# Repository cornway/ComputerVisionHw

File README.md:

## PCB deisgns with focus on computer vision for embedded devices

I will be publishing here open-source kicad PCB designs, with primary focus on computer vision for embedded (MCU)

Boards available:

1. stm32u5_v1.0 - utilizing stm32u5g9jxx mcu + ov2640 compatible camera and spi display; This board was made using schematics from stm32u5g9j_dk2 and stm32h7 "WeAct" development board
2. stm32u5_v2.0 - simplified version of stm32u5_v1.0, but seems target mcu is out of stock
3. stm32n6_v1.0 - based upon stm32n6xx nucleo development board, no psram yet; Length equalization tables for both xspi can be found in "Resources" directory

Each board is validated, to the best o my knowledge, but may have some issues.
Each board can be manufactured at JLCPCB (each component contains apropriate symbol designator) using Kicad add-on **com.github.bennymeg.JLC-Plugin-for-KiCad**, or in any other preferred way. Key point was to produce easy to understand design, that can be manufactured at low cost and used for further prototyping

Example (and not only) software for these boards can be found here :

https://github.com/cornway/ComputerVisionEmbedded

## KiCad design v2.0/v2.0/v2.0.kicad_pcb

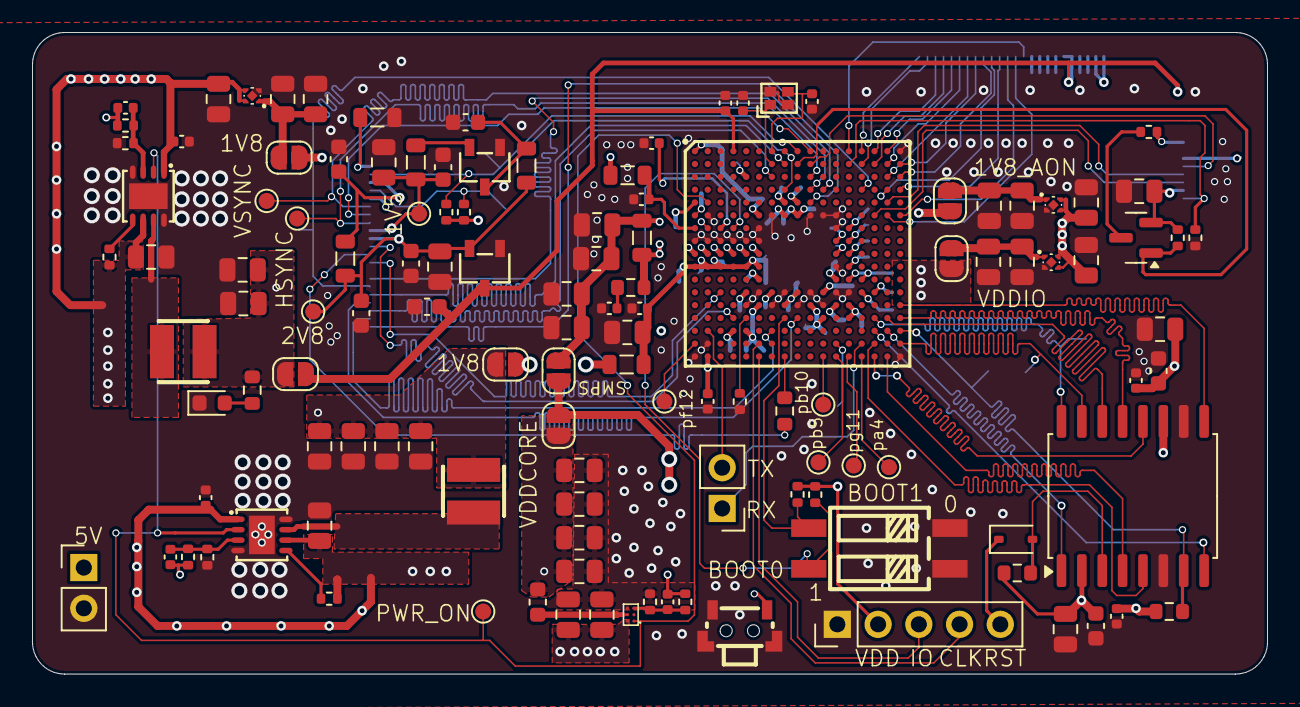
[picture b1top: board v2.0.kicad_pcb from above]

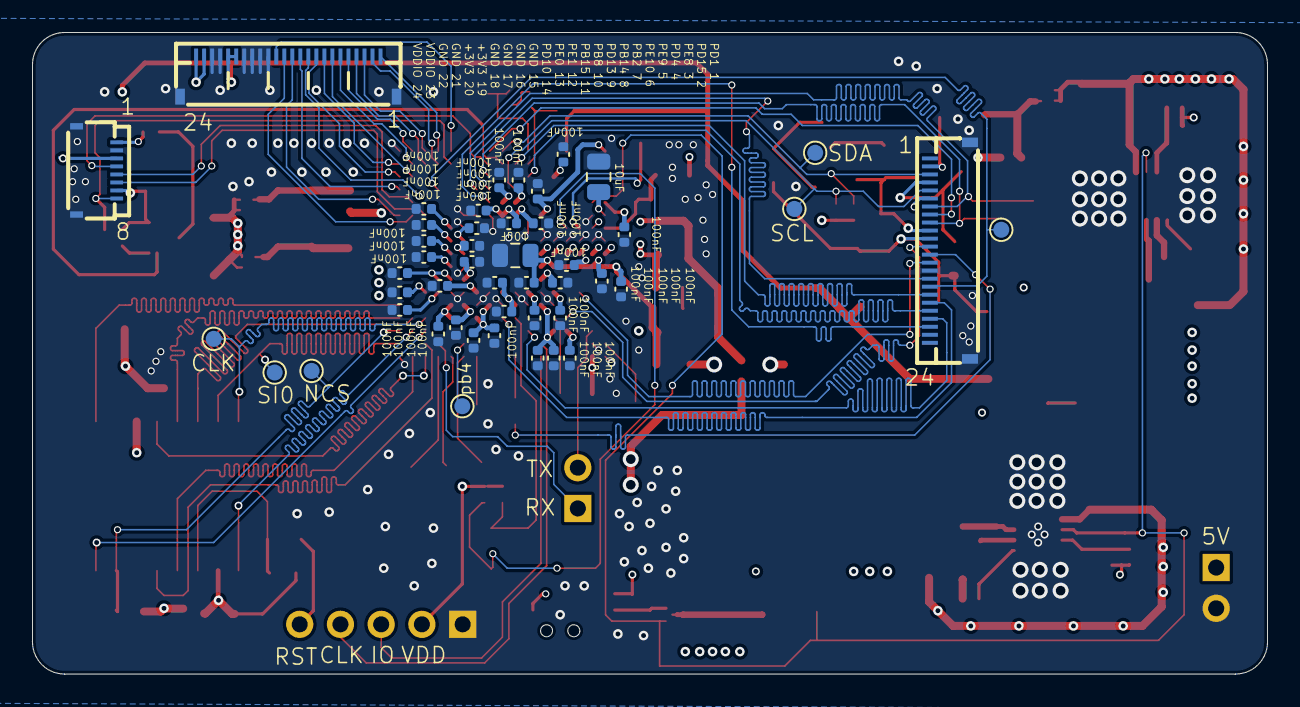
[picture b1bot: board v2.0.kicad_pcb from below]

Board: 4 copper layers, 77.0 x 40.0 mm, 170 parts (47 on the bottom side), 101 nets.

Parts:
C1, C6, C12, C15, C17, C18, C19, C20, C21, C22, C23, C25, C26, C27, C28, C29, C30, C31, C32, C33, C34, C35, C36, C37, C38, C39, C40, C41, C42, C43, C44, C45, C46, C47, C80, C81: 100nF; C_0402_1005Metric
C2, C4, C13, C14, C16, C51, C52: 1uF; C_0402_1005Metric
C3, C7, C9, C10, C54, C55, C56, C57, C58, C59, C60, C61, C63, C64: 22uF; C_0805_2012Metric
C5: 2.2nF; C_0402_1005Metric
C8, C11, C24, C48, C49, C50, C53, C90: 10uF; C_0805_2012Metric
C62, C65: 22p; C_0402_1005Metric
C66: 100pF; C_0402_1005Metric
C67, C68, C69, C70, C71, C72, C73, C74, C75: 1uF; C_0805_2012Metric
C76, C77: 4.7uf; C_0603_1608Metric
C78, C79, C84, C87: 10uf; C_0805_2012Metric
C82, C83, C86, C89: 1uf; C_0603_1608Metric
C85, C88: 100nf; C_0603_1608Metric
C91, C93: 8.2pF; C_0402_1005Metric
C92: 10nF; C_0402_1005Metric
D1: LED; LED_0603_1608Metric
D2: BAT60A; D_SOD-323
IC1: STM32N657X0H3Q; BGA264C80P17X17_1400X1400X100
J1: Conn_01x05_Pin; PinHeader_1x05_P2.54mm_Vertical
J2, J3: Conn_01x02_Pin; PinHeader_1x02_P2.54mm_Vertical
JP1, JP2, JP3, JP4, JP5, JP6, JP7: SolderJumper_2_Open; SolderJumper-2_P1.3mm_Open_RoundedPad1.0x1.5mm
L1: 1.0uH; L_0805_2012Metric
L2: 18@100Mhz; L_0805_2012Metric
L3: 2.2nH; L_0805_2012Metric
L4: 240nH; L_0603_1608Metric
L5, L6: 2.2uH; IND-SMD_L3.0-W3.0
L7, L8, L9, L10: 1.5uH; L_0805_2012Metric
Q1: SOT-23
R1, R2: 1k5; R_0402_1005Metric
R3, R4, R7, R8, R21: 10k; R_0402_1005Metric
R5: 2R; R_0603_1608Metric
R6: 200R; R_0402_1005Metric
R9: 75k; R_0402_1005Metric
R10, R15: 24k; R_0402_1005Metric
R11: 56k2; R_0402_1005Metric
R12: 160k; R_0402_1005Metric
R13: 5.1k; R_0603_1608Metric
R14: 30k; R_0402_1005Metric
R16: 10K; R_0603_1608Metric
R17: 100K; R_0603_1608Metric
R18: 33R; R_0603_1608Metric
R19: 100k; R_0402_1005Metric
R20: 22R; R_0402_1005Metric
SCL1: TestPoint; TestPoint_Pad_D1.0mm
SDA1: TestPoint; TestPoint_Pad_D1.0mm
SW1: SW-SMD_YZA-021
TP1, TP2, TP3, TP4, TP5, TP6, TP7, TP8, TP9, TP10, TP11, TP12, TP13, TP14, TP15: TestPoint; TestPoint_Pad_D1.0mm
U1: SW-SMD_SMXS-02K-TP
U2, U3: TDFN-8_L3.0-W3.0-P0.65-BL-EP
U4: TPS62088YFP; DSBGA-6_L0.8-W1.2-P0.40-R3-C2-TL
U5, U6, U7: UDFN-4_L1.0-W1.0-P0.65-TL
U8: MX66LM1G45G; SOIC-16W_7.5x10.3mm_P1.27mm
U9, U13: FFC-SMD_24P-P0.50_FH34SRJ-24S-0.5SH
U10: XC6206P282MR; SOT-23-3_L2.9-W1.6-P1.90-LS2.8-BR
U11: XC6206P152MR; SOT-23-3_L2.9-W1.6-P1.90-LS2.8-BR
U12: FPC-SMD_8P-P0.50_FH34D-8S-0.5SH-50
X1: -; CRYSTAL-SMD_4P-L1.6-W1.2-BL

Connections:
+3V3: C4.2, C82.1, C90.1, IC1.A4 (VDD33US_B), JP3.2 (B), Q1.2 (S), R21.1, U10.3 (VIN), U12.7, U13.19, U13.20
+5V: C48.1, C49.1, C50.1, C51.1, C52.1, C53.1, C67.1, C68.1, C69.1, J3.1, R7.1, R8.1, U2.1 (VINA), U2.6 (VINSW), U3.1 (VINA), U3.6 (VINSW), U4.A2 (VIN), U5.3 (EN), U5.4 (VIN), U6.3 (EN), U6.4 (VIN), U7.3 (EN), U7.4 (VIN)
/Flash/SI0: IC1.T17 (PN2), TP3.1, U8.15 (SI/SIO0)
/Flash/SI1: IC1.R15 (PN3), U8.8 (SO/SIO1)
/Flash/SI2: IC1.N17 (PN4), U8.9 (SIO2)
/Flash/SI3: IC1.R16 (PN5), U8.1 (SIO3)
/Flash/SI4: IC1.P16 (PN8), U8.14 (SIO4)
/Flash/SI5: IC1.T15 (PN9), U8.5 (SIO5)
/Flash/SI6: IC1.U15 (PN10), U8.12 (SIO6)
/Flash/SI7: IC1.U16 (PN11), U8.4 (SIO7)
/I2C1_SCL: IC1.D8 (PH9), R2.1, SCL1.1, U9.5
/I2C1_SDA: IC1.A9 (PC1), R1.1, SDA1.1, U9.3
/LCD/LCD_CS: IC1.B13 (PE7), R19.1, U12.8
/LCD/LCD_LEDA: R20.2, U12.1
/LCD/LCD_SCL: IC1.F15 (PE2), U12.6
/LCD/LCD_SDA: IC1.E16 (PB7), U12.5
/LCD/LCD_WR_RS: IC1.B10 (PC5), U12.4
/LCD/lcd_led: IC1.B9 (PC6), Q1.1 (G), R21.2
/MCU/BOOT0: IC1.G4 (BOOT0), R4.2, U1.4
/MCU/BOOT1: IC1.P8 (PA6), R3.2, U1.3
/MCU/DCMI_D0: IC1.P9 (PA1), U9.19
/MCU/DCMI_D1: IC1.R7 (PA10), U9.21
/MCU/DCMI_D2: IC1.E10 (PC3), U9.22
/MCU/DCMI_D3: IC1.C7 (PC9), U9.20
/MCU/DCMI_D4: IC1.B8 (PC11), U9.18
/MCU/DCMI_D5: IC1.D10 (PE4), U9.16
/MCU/DCMI_D6: IC1.M3 (PF5), U9.14
/MCU/DCMI_D7: IC1.P4 (PF1), U9.12
/MCU/DCMI_HSYNC: IC1.C10 (PC0), TP5.1, U9.9
/MCU/DCMI_PIXCLK: IC1.D14 (PD5), TP6.1, U9.17
/MCU/DCMI_VSYNC: IC1.D11 (PE6), TP4.1, U9.7
/MCU/MCO: IC1.U8 (PA8), R18.2
/MCU/OSC_IN: C93.2, IC1.A7 (PH0-_OSC_IN), X1.3 (OSC2)
/MCU/OSC_OUT: C91.1, IC1.B7 (PH1-_OSC_OUT), X1.1 (OSC1)
/MCU/OSPI_CLK: IC1.P15 (PN6), TP2.1, U8.16 (SCLK)
/MCU/OSPI_DQS: IC1.P17 (PN0), U8.13 (DQS)
/MCU/OSPI_NCS: IC1.R17 (PN1), R16.2, TP1.1, U8.7 (CS)
/MCU/PB2: IC1.C16 (PB2), U13.7
/MCU/PB8: IC1.D16 (PB8), U13.10
/MCU/PB14: IC1.B17 (PB14), U13.8
/MCU/PB15: IC1.D17 (PB15), U13.11
/MCU/PD1: IC1.A14 (PD1), U13.1
/MCU/PD4: IC1.B15 (PD4), U13.4
/MCU/PD10: IC1.A13 (PD10), U13.14
/MCU/PD13: IC1.C17 (PD13), U13.9
/MCU/PD15: IC1.B14 (PD15), U13.2
/MCU/PE0: IC1.F16 (PE0), U13.13
/MCU/PE1: IC1.F17 (PE1), U13.12
/MCU/PE8: IC1.A15 (PE8), U13.3
/MCU/PE9: IC1.A16 (PE9), U13.5
/MCU/PE10: IC1.B16 (PE10), U13.6
/MCU/PORTC_4: IC1.A10 (PC4), U9.8
/MCU/SWCLK: IC1.T6 (PA14), J1.4
/MCU/SWDIO: IC1.U6 (PA13), J1.3
/MCU/USART1_RX: IC1.T14 (PG8), J2.1
/MCU/USART1_TX: IC1.R2 (PF13), J2.2
/MCU/VDDA1V8PMU: C2.2, IC1.G1 (VDDA18P_MU), L2.2
/MCU/VDDSMPS: C11.1, C13.1, C14.1, C16.1, C19.1, C22.1, C24.1, IC1.K1 (VDDSMPS_1), IC1.K2 (VDDSMPS_2), IC1.K3 (VDDSMPS_3), IC1.K4 (VDDSMPS_4), IC1.K5 (VDDSMPS_5), IC1.K6 (VDDSMPS_6), L3.1
/MCU/VFBSMPS: C3.1, C7.1, C9.1, C10.1, IC1.G2 (VFBSMPS), JP7.1 (A), L1.2
/MCU/VLXSMPS: IC1.J1 (VLXSMPS_1), IC1.J2 (VLXSMPS_2), IC1.J3 (VLXSMPS_3), IC1.J4 (VLXSMPS_4), IC1.J5 (VLXSMPS_5), IC1.J6 (VLXSMPS_6), L1.1, R5.1
/RESET: C92.1, D2.1 (K), IC1.G3 (NRST), J1.5, SW1.1, U9.6, U12.3
/VDDA_1V8: C15.1, C21.1, C26.1, C29.1, C31.1, C34.1, IC1.C5 (VDDA18U_SB), IC1.M5 (VDDA18P_LL), IC1.N6 (VDDA18A_DC), IC1.N13 (VDDIO3_1), IC1.P13 (VDDIO3_2), IC1.R5 (VDDA18C_SI), IC1.U2 (VREF+), JP5.2 (B), L2.1
/VDDA_1V8_AON: C6.2, IC1.A1 (PDR_ON), IC1.F6 (VDDA18A_ON), JP1.2 (B)
/VDDCORE: C18.1, C23.1, C27.1, C30.1, C33.1, C36.1, C38.1, C40.1, C42.1, C43.1, IC1.L6 (VDDCORE_1), IC1.L12 (VDDCORE_2), IC1.M7 (VDDCORE_3), IC1.M9 (VDDCORE_4), IC1.M11 (VDDCORE_5), IC1.N8 (VDDCORE_6), IC1.N10 (VDDCORE_7), IC1.N12 (VDDCORE_8), IC1.P11 (VDDCORE_9), IC1.R4 (VDDCSI), JP6.2 (B), JP7.2 (B)
/VDDIO: C1.2, C12.1, C17.1, C20.1, C25.1, C28.1, C32.1, C35.1, C37.1, C39.1, C41.1, C44.1, C45.1, C46.1, C47.1, IC1.E1 (VBAT), IC1.E8 (VDDIO4_1), IC1.E9 (VDDIO5_1), IC1.F8 (VDDIO4_2), IC1.F9 (VDDIO5_2), IC1.G13 (VDD_1), IC1.H12 (VDD_2), IC1.H13 (VDD_3), IC1.J12 (VDD_4), IC1.J13 (VDD_5), IC1.K13 (VDD_6), IC1.L13 (VDDIO2_1), IC1.L14 (VDDIO2_2), IC1.M14 (VDDIO2_3), IC1.M15 (VDDIO2_4), J1.2, JP2.2 (B), R1.2, R2.2, R3.1, R4.1, U13.23, U13.24
/VDD_1V8: C76.1, C77.1, C78.1, C79.1, C80.1, C81.1, JP4.2 (B), L3.2, R16.1, R17.1, U8.2 (VCC), U8.11 (VCC)
/camera/AGND: L8.1, U9.2
/camera/AVDD-2V8: C89.1, L10.2, U9.4
/camera/DVDD-1V5: C87.1, C88.1, L9.2, TP8.1, U9.10
/camera_power/VDD_2V8: C84.1, C85.1, C86.1, L7.1, L10.1, TP7.1, U9.11, U10.2 (VOUT)
/power/FB: C66.2, R11.2, R12.1, U4.C1 (FB)
/power/FB2: C65.2, R14.2, R15.1, U2.3 (FB)
/power/FB3: C62.2, R9.2, R10.1, U3.3 (FB)
/power/PWR_ON: IC1.E2 (PWR_ON), TP9.1, U2.2 (EN), U3.2 (EN), U4.A1 (EN)
/power/VDDA_1V8: C72.1, C75.1, JP5.1 (A), U7.1 (VOUT)
/power/VDDA_1V8_AON: C71.1, C74.1, JP1.1 (A), U6.1 (VOUT)
/power/VDDCORE: C54.1, C57.1, C60.1, C63.1, C66.1, JP6.1 (A), L4.2, R11.1
/power/VDDIO: C70.1, C73.1, JP2.1 (A), U5.1 (VOUT)
/power/VDD_1V8: C55.1, C58.1, C61.1, C64.1, C65.1, JP4.1 (A), L5.2, R14.1
/power/VDD_3V3: C56.1, C59.1, C62.1, JP3.1 (A), L6.2, R9.1, R13.1
GND: C1.1, C2.1, C3.2, C4.1, C5.2, C6.1, C7.2, C8.1, C9.2, C10.2, C11.2, C12.2, C13.2, C14.2, C15.2, C16.2, C17.2, C18.2, C19.2, C20.2, C21.2, C22.2, C23.2, C24.2, C25.2, C26.2, C27.2, C28.2, C29.2, C30.2, C31.2, C32.2, C33.2, C34.2, C35.2, C36.2, C37.2, C38.2, C39.2, C40.2, C41.2, C42.2, C43.2, C44.2, C45.2, C46.2, C47.2, C48.2, C49.2, C50.2, C51.2, C52.2, C53.2, C54.2, C55.2, C56.2, C57.2, C58.2, C59.2, C60.2, C61.2, C63.2, C64.2, C67.2, C68.2, C69.2, C70.2, C71.2, C72.2, C73.2, C74.2, C75.2, C76.2, C77.2, C78.2, C79.2, C80.2, C81.2, C82.2, C83.2, C84.2, C85.2, C86.2, C87.2, C88.2, C89.2, C90.2, C91.2, C92.2, C93.1, D1.1 (K), IC1.A17 (VSS_1), IC1.F2 (VSSAPMU), IC1.F7 (VSS_2), IC1.F10 (VSS_3), IC1.F11 (VSS_4), IC1.F12 (VSS_5), IC1.G6 (VSSAON), IC1.G12 (VSS_6), IC1.H1 (VSSSMPS_1), IC1.H2 (VSSSMPS_2), IC1.H3 (VSSSMPS_3), IC1.H4 (VSSSMPS_4), IC1.H5 (VSSSMPS_5), IC1.H6 (VSSSMPS_6), IC1.K12 (VSS_7), IC1.M6 (VSSA), IC1.M8 (VSS_8), IC1.M10 (VSS_9), IC1.M12 (VSS_10), IC1.M13 (VSS_11), IC1.N5 (VSS_12), IC1.N7 (VSS_13), IC1.N9 (VSS_14), IC1.N11 (VSS_15), IC1.T2 (VREF-), IC1.U1 (VSS_16), IC1.U17 (VSS_17), J1.1, J3.2, L8.2, R6.2, R10.2, R12.2, R15.2, R19.2, SW1.2, SW1.3, SW1.4, U1.1, U1.2, U2.4 (AGND), U2.8 (PGND), U2.9 (EP), U3.4 (AGND), U3.8 (PGND), U3.9 (EP), U4.C2 (GND), U5.2 (GND), U5.5 (EP), U6.2 (GND), U6.5 (EP), U7.2 (GND), U7.5 (EP), U8.6 (GND), U8.10 (GND), U9.15, U9.25, U9.26, U10.1 (VSS), U11.1 (GND), U12.2, U12.9, U12.10, U13.15, U13.16, U13.17, U13.18, U13.21, U13.22, U13.25, U13.26, X1.2, X1.4
unnamed: C5.1, R5.2
unnamed: D1.2 (A), R13.2
unnamed: D2.2 (A), R17.2, U8.3 (RESET)
unnamed: IC1.P5 (CSI_REXT), R6.1
unnamed: IC1.U14 (PA4), TP10.1
unnamed: IC1.T12 (PB4), TP14.1
unnamed: IC1.U12 (PB5), TP12.1
unnamed: IC1.U11 (PB10), TP13.1
unnamed: IC1.T1 (PF12), TP15.1
unnamed: IC1.U13 (PG11), TP11.1
unnamed: C8.2, IC1.F1 (V08CAP)
unnamed: Q1.3 (D), R20.1
unnamed: R18.1, U9.13
unnamed: R7.2, U2.5 (PG)
unnamed: L5.1, U2.7 (SW)
unnamed: R8.2, U3.5 (PG)
unnamed: L6.1, U3.7 (SW)
unnamed: L4.1, U4.B2 (SW)
unnamed: C83.1, L7.2, U11.3 (Vin)
unnamed: L9.1, U11.2 (Vout)

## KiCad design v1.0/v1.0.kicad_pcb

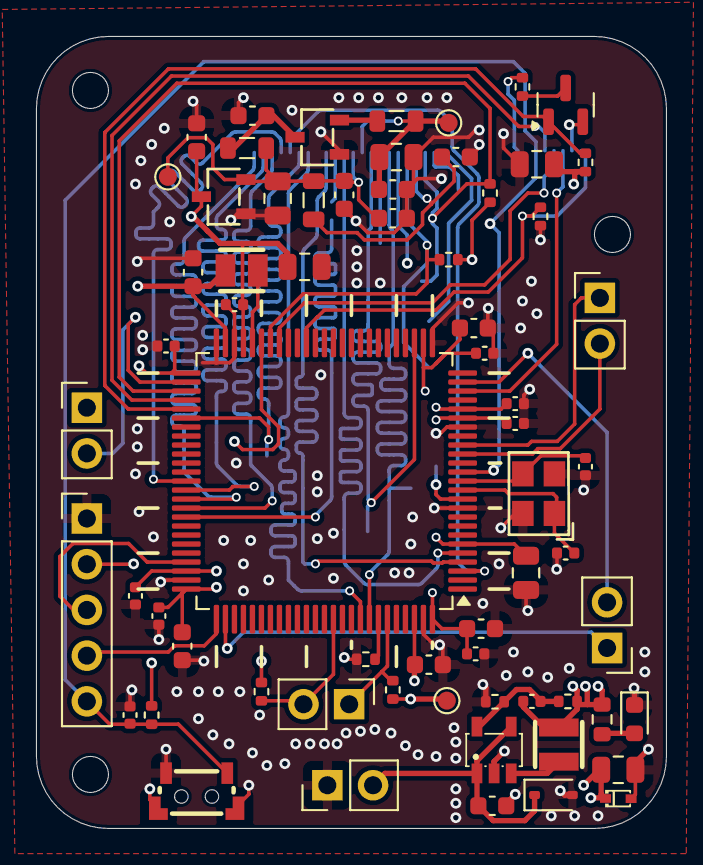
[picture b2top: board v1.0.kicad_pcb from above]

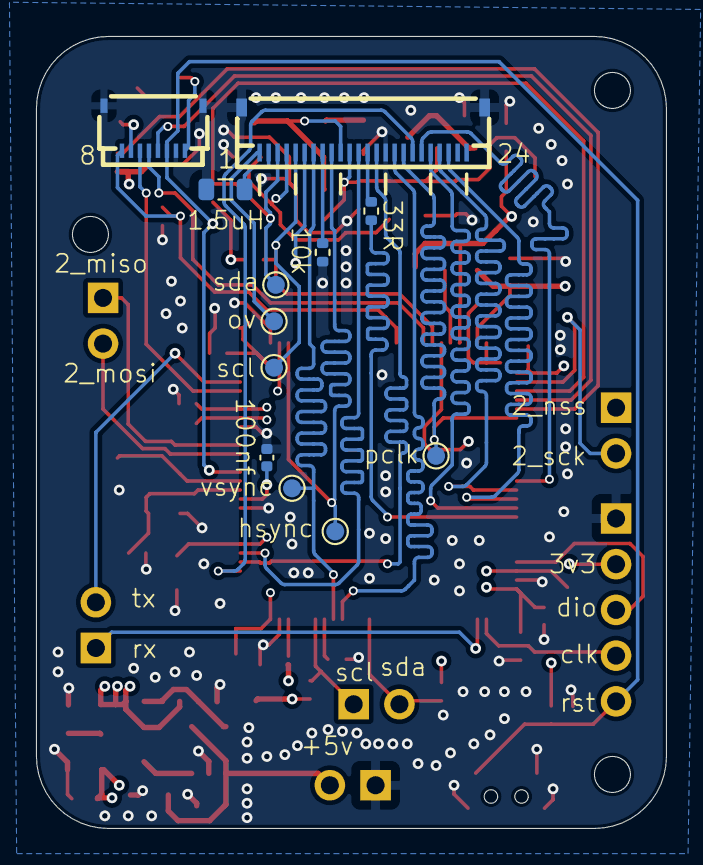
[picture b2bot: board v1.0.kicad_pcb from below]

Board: 4 copper layers, 35.0 x 44.0 mm, 78 parts (12 on the bottom side), 52 nets.

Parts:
C7, C26, C37: 10uF; C_0805_2012Metric
C8: 4.7uf; C_0603_1608Metric
C9, C10, C14, C17: 1uf; C_0603_1608Metric
C11, C13, C18: 10uf; C_0805_2012Metric
C12, C15: 100nf; C_0603_1608Metric
C16: 22pf; C_0402_1005Metric
C19, C22: 8.2pF; C_0402_1005Metric
C24, C29, C30, C32, C33, C34, C38, C39, C40, C41: 100nF; C_0402_1005Metric
C27: 4.7uF; C_0603_1608Metric
C28: 1uF; C_0603_1608Metric
C31: 100nF; C_0603_1608Metric
C35, C36: 2.2uF; C_0603_1608Metric
D3: LESD3Z5.0T1G; D_SOD-323
D4: LED; LED_0603_1608Metric
D5: LESD5Z3.3T1G; SOD-523F_L1.2-W0.8-LS1.7-RD
IC1: STM32U5G7VJT6Q; LQFP-100_14x14mm_P0.5mm
J1: Conn_01x05_Pin; PinHeader_1x05_P2.54mm_Vertical
J3, J4, J5, J6, J7: Conn_01x02_Pin; PinHeader_1x02_P2.54mm_Vertical
L1: 2.2uH; IND-SMD_L2.4-W1.7_NL201614
L2, L3, L5, L6: 1.5uH; L_0805_2012Metric
L4: 2.2uH; IND-SMD_L2.5-W2.0_SWPA252012S
Q2: SOT-23
R11, R12, R24, R25: 4K7; R_0402_1005Metric
R13, R23: 100k; R_0402_1005Metric
R14: 22R; R_0402_1005Metric
R15: 10k; R_0402_1005Metric
R16: 680k; R_0402_1005Metric
R17: 150k; R_0402_1005Metric
R18: 5.1k; R_0603_1608Metric
R19, R21: 10K; R_0402_1005Metric
R20: 33R; R_0402_1005Metric
SCL1: TestPoint; TestPoint_Pad_D1.0mm
SDA1: TestPoint; TestPoint_Pad_D1.0mm
SW1: SW-SMD_YZA-021
TP2, TP3, TP4, TP5, TP6, TP7, TP8: TestPoint; TestPoint_Pad_D1.0mm
U5: FPC-SMD_8P-P0.50_FH34D-8S-0.5SH-50
U6: XC6206P152MR; SOT-23-3_L2.9-W1.6-P1.90-LS2.8-BR
U7: XC6206P282MR; SOT-23-3_L2.9-W1.6-P1.90-LS2.8-BR
U8: SY8088AAC; SOT-23-5_L3.0-W1.7-P0.95-LS2.8-BR
U9: FFC-SMD_24P-P0.50_FH34SRJ-24S-0.5SH
X2: 16MHz; CRYSTAL-SMD_4P-L3.2-W2.5-BL-1

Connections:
+1V5: C13.1, C15.1, L3.2, TP3.1, U9.10
+2V8: C11.1, C12.1, C14.1, L2.1, L5.1, TP2.1, U7.2 (VOUT), U9.11
+3V3: C7.1, C9.1, C16.1, C18.1, C26.2, C27.2, C28.2, C29.2, C30.2, C31.2, C32.2, C33.2, C34.2, C37.2, C38.2, C39.2, C40.2, C41.2, D5.1 (C), IC1.6 (VBAT), IC1.11 (VDD_1), IC1.20 (VREF+), IC1.21 (VDDA), IC1.27 (VDD_2), IC1.47 (VDDSMPS), IC1.51 (VDD_3), IC1.73 (VDDUSB), IC1.75 (VDD_4), IC1.100 (VDD_5), J1.2, L4.2, Q2.2 (S), R11.1, R12.1, R15.1, R16.1, R18.1, R23.1, R24.1, R25.1, TP4.1, U5.7, U7.3 (VIN)
+5V: C8.1, D3.1, J7.2, U8.1 (EN), U8.4 (IN)
/DVP_HSYNC: IC1.28 (PA4), TP6.1, U9.9
/DVP_PCLK: IC1.56 (PD9), TP7.1, U9.17
/DVP_VSYNC: IC1.93 (PB7), TP5.1, U9.7
/DVP_XCLK: IC1.67 (PA8), R20.2
/LCD/LCD_CS: IC1.40 (PE12), R13.1, U5.8
/LCD/LCD_LEDA: R14.2, U5.1
/LCD/LCD_SCL: IC1.23 (PA1), U5.6
/LCD/LCD_SDA: IC1.43 (PE15), U5.5
/LCD/LCD_WR_RS: IC1.54 (PB15), U5.4
/LCD/lcd_led: IC1.55 (PD8), Q2.1 (G), R15.2
/MCU/DCMI_D0: IC1.63 (PC6), U9.19
/MCU/DCMI_D1: IC1.64 (PC7), U9.21
/MCU/DCMI_D2: IC1.65 (PC8), U9.22
/MCU/DCMI_D3: IC1.66 (PC9), U9.20
/MCU/DCMI_D4: IC1.3 (PE4), U9.18
/MCU/DCMI_D5: IC1.92 (PB6), U9.16
/MCU/DCMI_D6: IC1.4 (PE5), U9.14
/MCU/DCMI_D7: IC1.5 (PE6), U9.12
/MCU/I2C1_SCL: IC1.95 (PB8), J6.1, R25.2
/MCU/I2C1_SDA: IC1.89 (PB3), J6.2, R24.2
/MCU/I2C2_SCL: IC1.44 (PB10), R12.2, SCL1.1, U9.5
/MCU/I2C2_SDA: IC1.53 (PB14), R11.2, SDA1.1, U9.3
/MCU/RCC_OSC_IN: C19.1, IC1.12 (PH0-OSC_IN), X2.1 (OSC1)
/MCU/RCC_OSC_OUT: C22.2, IC1.13 (PH1-OSC_OUT), X2.3 (OSC2)
/MCU/SPI2_MISO: IC1.17 (PC2), J5.1
/MCU/SPI2_MOSI: IC1.16 (PC1), J5.2
/MCU/SPI2_NSS: IC1.45 (PB11), J4.1
/MCU/SPI2_SCK: IC1.52 (PB13), J4.2
/MCU/SWCLK: IC1.76 (PA14), J1.4
/MCU/SWDIO: IC1.72 (PA13), J1.3
/MCU/USART2_RX: IC1.77 (PA15), J3.1
/MCU/USART2_TX: IC1.24 (PA2), J3.2
/MCU/VDD11: C35.2, C36.2, IC1.49 (VDD11_1), IC1.98 (VDD11_2), L1.1
/RESET: C24.1, IC1.14 (NRST), J1.5, R23.2, SW1.1, U5.3, U9.6
/camera/AVDD-2V8: C17.1, L5.2, U9.4
/camera/OV_STROBE: TP8.1, U9.1
GND: C7.2, C8.2, C9.2, C10.2, C11.2, C12.2, C13.2, C14.2, C15.2, C17.2, C18.2, C19.2, C22.1, C24.2, C26.1, C27.1, C28.1, C29.1, C30.1, C31.1, C32.1, C33.1, C34.1, C35.1, C36.1, C37.1, C38.1, C39.1, C40.1, C41.1, D3.2, D4.1 (K), D5.2 (A), IC1.10 (VSS_1), IC1.19 (VSSA), IC1.26 (VSS_2), IC1.48 (VSSSMPS), IC1.50 (VSS_3), IC1.74 (VSS_4), IC1.99 (VSS_5), J1.1, J7.1, L6.2, R13.2, R17.2, R19.2, R21.2, SW1.2, SW1.3, SW1.4, U5.2, U5.9, U5.10, U6.1 (GND), U7.1 (VSS), U8.2 (GND), U9.15, U9.25, U9.26, X2.2 (GND), X2.4 (GND)
GNDA: L6.1, U9.2
unnamed: D4.2 (A), R18.2
unnamed: IC1.94 (PH3-BOOT0), R21.1
unnamed: IC1.46 (VLXSMPS), L1.2
unnamed: Q2.3 (D), R14.1
unnamed: R19.1, U9.8
unnamed: R20.1, U9.13
unnamed: C10.1, L2.2, U6.3 (Vin)
unnamed: L3.1, U6.2 (Vout)
unnamed: C16.2, R16.2, R17.1, U8.5 (FB)
unnamed: L4.1, U8.3 (LX)

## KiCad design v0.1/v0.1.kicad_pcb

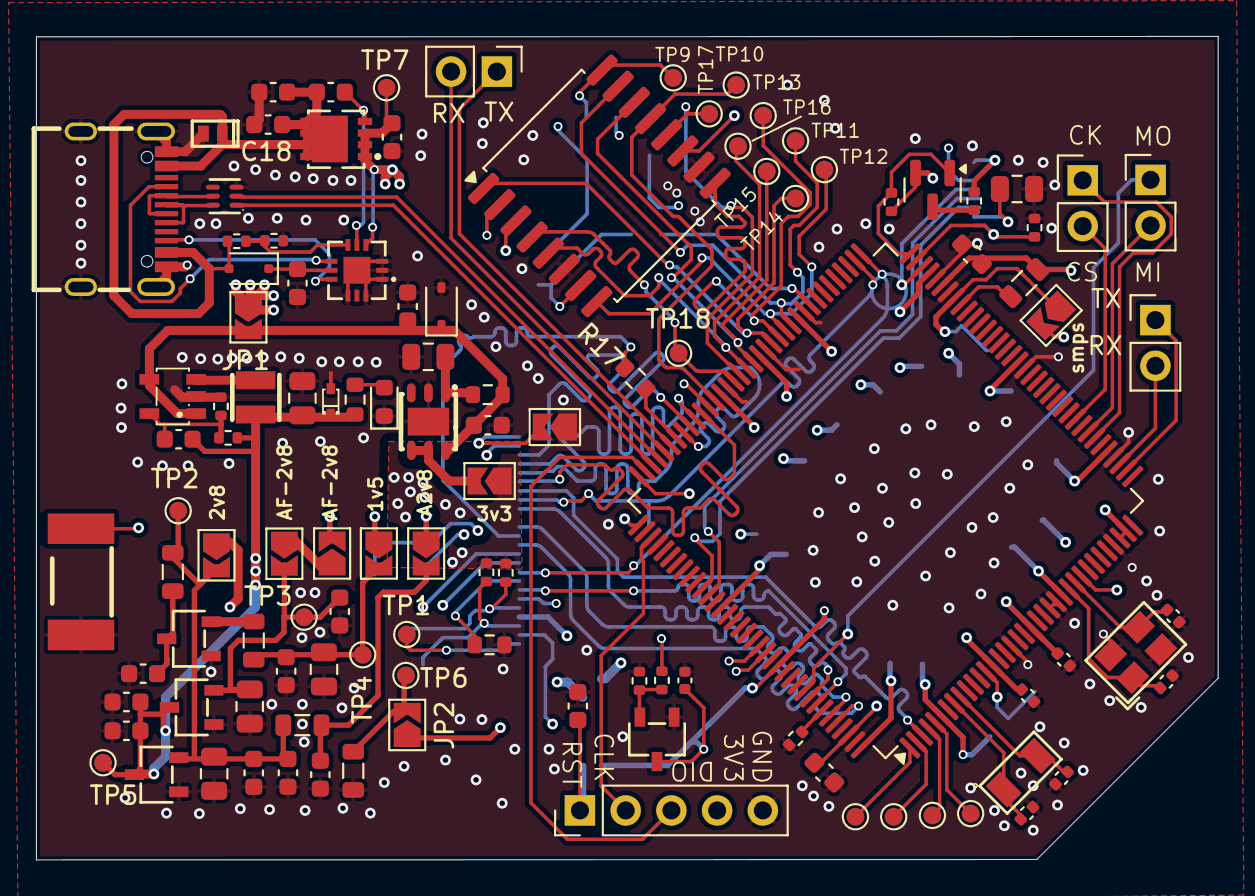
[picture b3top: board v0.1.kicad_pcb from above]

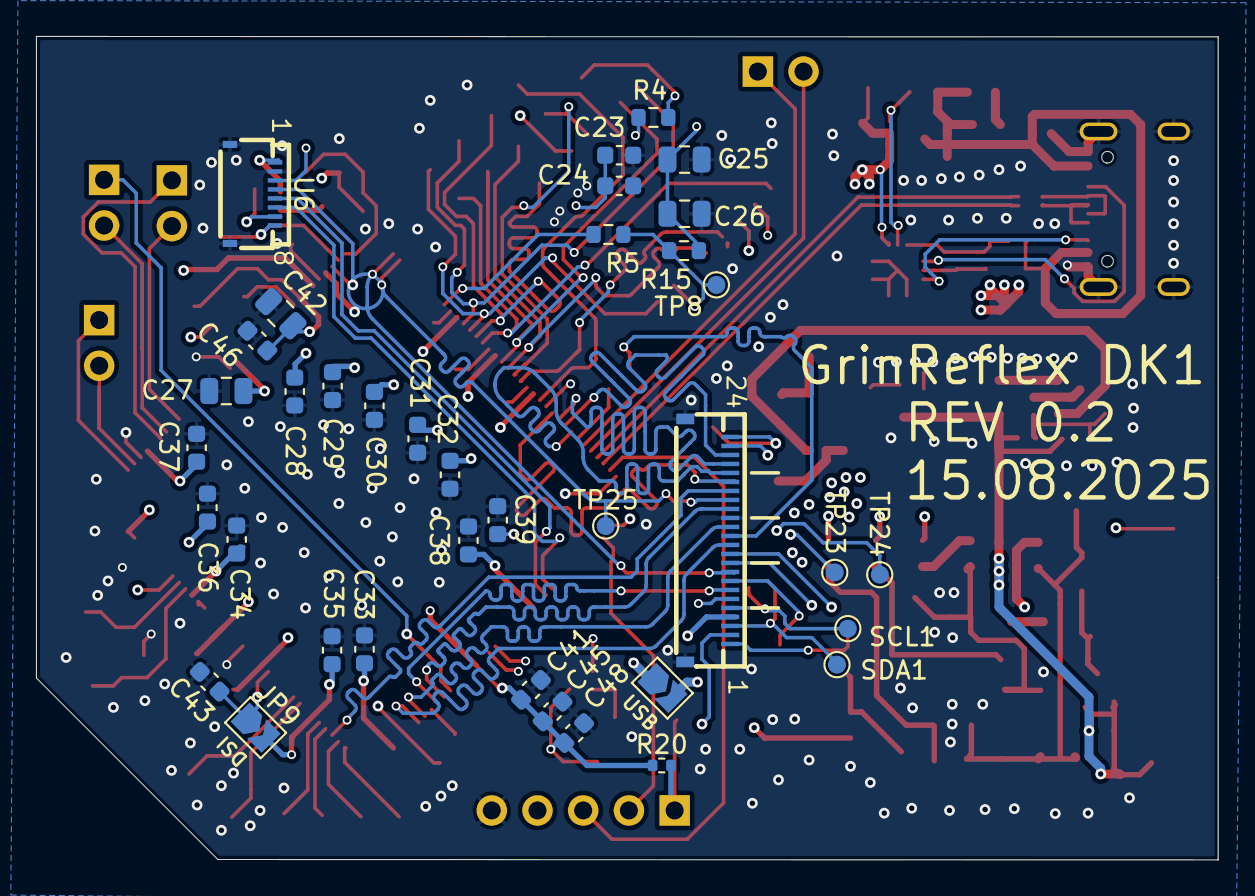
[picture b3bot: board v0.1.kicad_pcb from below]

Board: 4 copper layers, 65.7 x 45.8 mm, 148 parts (37 on the bottom side), 97 nets.

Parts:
C1, C15, C23, C24, C41: 4.7uf; C_0603_1608Metric
C2, C3, C4, C9, C12: 1uf; C_0603_1608Metric
C5, C7, C8, C14, C25, C26, C27, C42: 10uf; C_0805_2012Metric
C6, C10, C11, C28, C29, C30, C31, C32, C33, C34, C35, C36, C37, C38, C39, C43, C45, C46, C48: 100nf; C_0603_1608Metric
C13: 22pf; C_0603_1608Metric
C16: 100nF; C_0805_2012Metric
C17: 10uF; C_0805_2012Metric
C18: 100pF; C_0603_1608Metric
C19: 1uF; C_0603_1608Metric
C20: 470pF; C_0603_1608Metric
C21, C22, C55: 100nF; C_0603_1608Metric
C40, C44: 2.2uf; C_0603_1608Metric
C47, C49, C54: 100nf; C_0402_1005Metric
C50, C53: 8.2pF; C_0402_1005Metric
C51, C52: 3.3pF; C_0402_1005Metric
D1: LESD3Z5.0T1G; D_SOD-323
D2: LED; LED_0603_1608Metric
D3: LESD5Z3.3T1G; SOD-523F_L1.2-W0.8-LS1.7-RD
D4: ESDA25P35-1U1M; DFN1610-2_L1.6-W1.0-P1.05-RD
D5: BAT54J; D_SOD-323F
J1: Conn_01x05_Pin; PinHeader_1x05_P2.54mm_Vertical
J2, J3, J4, J5: Conn_01x02_Pin; PinHeader_1x02_P2.54mm_Vertical
JP1, JP2, JP3, JP4, JP5, JP6, JP7, JP8, JP9, JP10, JP11, JP12: SolderJumper_2_Open; SolderJumper-2_P1.3mm_Open_TrianglePad1.0x1.5mm
L1, L2, L4, L5: 1.5uH; L_0805_2012Metric
L3: 2.2uH; IND-SMD_L2.5-W2.0_SWPA252012S
L6: ECMF02-2AMX6; UFQFN-6_L1.7-W1.5
L7: 2.2uH; L_0805_2012Metric
Q1: SOT-23
Q2: PDFN-8_L3.1-W3.0-P0.65-LS3.3-BL
R1, R2: 4.7k; R_0402_1005Metric
R3, R9: 10k; R_0603_1608Metric
R4, R5, R17: 33R; R_0603_1608Metric
R6: 680k; R_0402_1005Metric
R7: 150k; R_0402_1005Metric
R8: 5.1k; R_0603_1608Metric
R10, R18, R20: 100k; R_0402_1005Metric
R11: 22R; R_0402_1005Metric
R12, R13, R16: 10k; R_0402_1005Metric
R14: 2.4k; R_0402_1005Metric
R15: 10K; R_0603_1608Metric
R19: 1.5k; R_0402_1005Metric
SCL1: TestPoint; TestPoint_Pad_D1.0mm
SDA1: TestPoint; TestPoint_Pad_D1.0mm
SW1: KEY-SMD_KSS-2G
TP1, TP2, TP3, TP4, TP5, TP6, TP7, TP8, TP9, TP10, TP11, TP12, TP13, TP14, TP15, TP16, TP17, TP18, TP19, TP20, TP21, TP22, TP23, TP24, TP25: TestPoint; TestPoint_Pad_D1.0mm
U1: XC6206P152MR; SOT-23-3_L2.9-W1.6-P1.90-LS2.8-BR
U2, U4: XC6206P282MR; SOT-23-3_L2.9-W1.6-P1.90-LS2.8-BR
U3: SY8088AAC; SOT-23-5_L3.0-W1.7-P0.95-LS2.8-BR
U5: DFN-6_L3.0-W3.0-P0.95-BL-EP-1
U6: FPC-SMD_8P-P0.50_FH34D-8S-0.5SH-50
U7: USB-TYPE-C-SMD_C9900008089
U8: QFN-12_L3.0-W3.0-P0.50-BL-EP1.5
U9: MX66LM1G45G; SOIC-16W_7.5x10.3mm_P1.27mm
U10: STM32U5G9ZJTxQ; LQFP-144_20x20mm_P0.5mm
U11: FFC-SMD_24P-P0.50_FH34SRJ-24S-0.5SH
U12: SOT-23-3_L2.9-W1.6-P1.90-LS2.8-BR
X1: 32.768kHz; OSC-SMD_2P-L3.2-W1.5
X2: 16MHz; CRYSTAL-SMD_4P-L3.2-W2.5-BL-1

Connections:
/2v8: JP6.1 (A), U11.11
/3v3_pwr: C17.1, C23.1, C24.1, C25.1, C26.1, C27.1, C28.2, C29.1, C30.2, C31.1, C32.2, C33.1, C34.2, C35.1, C36.2, C37.1, C38.2, C41.1, C45.1, C48.1, C54.2, J1.4, JP7.1 (A), JP8.2 (B), JP9.2 (B), JP10.2 (B), Q1.2 (S), R1.1, R2.1, R12.1, R15.1, R20.1, U6.7, U9.2 (VCC), U9.11 (VCC), U10.6 (VBAT), U10.25 (VDD), U10.34 (VREF+), U10.35 (VDDA), U10.41 (VDD), U10.55 (VDD), U10.69 (VDD), U10.83 (VDD), U10.89 (VDD), U10.95 (VDD), U10.109 (VDD), U10.122 (VDD), U10.131 (VDDIO2), U10.144 (VDD), U12.3 (VCC)
/+5V: C21.1, JP1.1 (A), Q2.1 (S), Q2.2 (S), Q2.3 (S), TP7.1, U8.4 (SOURCE)
/AF-2v8: JP3.1 (A), JP11.1 (A)
/AVDD-2v8: JP4.1 (A), U11.4
/Camera/DVP_D0: U10.98 (PC6), U11.19
/Camera/DVP_D1: U10.99 (PC7), U11.21
/Camera/DVP_D2: U10.100 (PC8), U11.22
/Camera/DVP_D3: U10.101 (PC9), U11.20
/Camera/DVP_D4: U10.3 (PE4), U11.18
/Camera/DVP_D5: U10.136 (PB6), U11.16
/Camera/DVP_D6: U10.139 (PB8), U11.14
/Camera/DVP_D7: U10.140 (PB9), U11.12
/Camera/DVP_HSYNC: TP24.1, U10.73 (PD8), U11.9
/Camera/DVP_PCLK: TP25.1, U10.74 (PD9), U11.17
/Camera/DVP_PWDN: R3.1, U11.8
/Camera/DVP_VSYNC: TP23.1, U10.137 (PB7), U11.7
/Camera/DVP_XCLK: R17.2, U10.102 (PA8)
/Camera/OV_STROBE: TP1.1, U11.1
/Clock_Reset/OSC32_1: C51.1, U10.8 (PC14), X1.1 (OSC1)
/Clock_Reset/OSC32_2: C52.1, U10.9 (PC15), X1.2 (OSC2)
/Clock_Reset/OSC_1: C50.1, U10.26 (PH0), X2.1 (OSC1)
/Clock_Reset/OSC_2: C53.2, U10.27 (PH1), X2.3 (OSC2)
/DVDD-1v5: JP5.1 (A), U11.10
/FLASH/CS: R5.2, R15.2, TP8.1, U9.7 (CS)
/FLASH/DQS: TP10.1, U9.13 (DQS), U10.96 (PI2)
/FLASH/SCLK: R4.2, TP9.1, U9.16 (SCLK)
/FLASH/SI0: TP11.1, U9.15 (SI/SIO0), U10.84 (PH10)
/FLASH/SI1: TP12.1, U9.8 (SO/SIO1), U10.85 (PH11)
/FLASH/SI2: TP13.1, U9.9 (SIO2), U10.86 (PH12)
/FLASH/SI3: TP14.1, U9.1 (SIO3), U10.87 (PH13)
/FLASH/SI4: TP15.1, U9.14 (SIO4), U10.90 (PH14)
/FLASH/SI5: TP16.1, U9.5 (SIO5), U10.91 (PH15)
/FLASH/SI6: TP17.1, U9.12 (SIO6), U10.92 (PI0)
/FLASH/SI7: TP18.1, U9.4 (SIO7), U10.93 (PI1)
/GNDA: JP2.1 (A), U11.2
/I2C1_SCL: R1.2, SCL1.1, U10.129 (PG14), U11.5
/I2C1_SDA: R2.2, SDA1.1, U10.128 (PG13), U11.3
/LCD/LCD_CS: R10.1, U6.8, U10.71 (PB14)
/LCD/LCD_LEDA: R11.2, U6.1
/LCD/LCD_SCL: U6.6, U10.119 (PD3)
/LCD/LCD_SDA: U6.5, U10.120 (PD4)
/LCD/LCD_WR_RS: U6.4, U10.70 (PB13)
/LCD/lcd_led: Q1.1 (G), R12.2, U10.72 (PB15)
/MCU/SWCLK: J1.2, U10.111 (PA14)
/MCU/SWDIO: J1.3, U10.107 (PA13)
/MCU/USBC_HS_N: L6.2 (D-), U10.105 (PA11)
/MCU/USBC_HS_P: L6.1 (D+), U10.106 (PA12)
/MCU/VDD11: C40.1, C44.1, C47.1, C49.1, L7.2, U10.14 (VDD11DSI), U10.20 (VDD11DSI), U10.67 (VDD11), U10.142 (VDD11)
/MCU/VDDDSI: C43.1, JP9.1 (A), U10.13 (VDDDSI)
/MCU/VDDSMPS: C42.1, C46.1, JP8.1 (A), U10.65 (VDDSMPS)
/MCU/VDDUSB: C39.1, JP10.1 (A), U10.108 (VDDUSB)
/MCU/hspi1_clk: R4.1, U10.97 (PI3)
/MCU/hspi1_ncs: R5.1, U10.81 (PH9)
/MCU/spi1_miso: J2.2, U10.44 (PA6)
/MCU/spi1_mosi: J2.1, U10.135 (PB5)
/MCU/spi1_nss: J3.2, U10.46 (PB0)
/MCU/spi1_sck: J3.1, U10.43 (PA5)
/MCU/usart1_rx: J4.2, U10.104 (PA10)
/MCU/usart1_tx: J4.1, U10.103 (PA9)
/MCU/usart2_rx: J5.2, U10.39 (PA3)
/MCU/usart2_tx: J5.1, U10.38 (PA2)
/Power/2v8: C5.1, C6.1, C9.1, JP6.2 (B), L1.1, L4.1, TP2.1, U2.2 (VOUT)
/Power/3v3: C2.1, C4.1, C13.1, C14.1, D3.1 (C), L3.2, R6.1, R8.1, TP5.1, U2.3 (VIN), U4.3 (VIN)
/Power/3v3_pwr: JP7.2 (B), U5.4 (VO), U5.5 (VO_SENSE)
/Power/+5V: C1.1, C15.1, D1.1, JP1.2 (B), R9.2, U3.1 (EN), U3.4 (IN), U5.6 (VI)
/Power/AF-2v8: C7.1, C10.1, JP3.2 (B), TP3.1, U4.2 (VOUT)
/Power/AVDD-2v8: C12.1, JP4.2 (B), L4.2
/Power/DVDD-1v5: C8.1, C11.1, JP5.2 (B), L2.2, TP4.1
/RESET: C55.1, J1.1, R19.2, R20.2, SW1.2, U6.3, U9.3 (RESET), U10.28 (NRST), U11.6
/USB-C/CC1: U7.A5 (CC1), U8.7 (CC1c)
/USB-C/CC2: U7.B5 (CC2), U8.9 (CC2c)
/USB-C/USB_DN: L6.5 (D-), U7.A7 (DN1), U7.B7 (DN2)
/USB-C/USB_DP: L6.6 (D+), U7.A6 (DP1), U7.B6 (DP2)
/USB-C/VBUS: C18.1, C19.1, C20.1, D4.1, D5.2 (A), Q2.5 (D), Q2.6 (D), Q2.7 (D), Q2.8 (D), Q2.9 (D), R13.1, U7.A4B9 (VBUS), U7.B4A9 (VBUS)
GND: C1.2, C2.2, C3.2, C4.2, C5.2, C6.2, C7.2, C8.2, C9.2, C10.2, C11.2, C12.2, C14.2, C15.2, C16.2, C17.2, C18.2, C19.2, C21.2, C22.2, C23.2, C24.2, C25.2, C26.2, C27.2, C28.1, C29.2, C30.1, C31.2, C32.1, C33.2, C34.1, C35.2, C36.1, C37.2, C38.1, C39.2, C40.2, C41.2, C42.2, C43.2, C44.2, C45.2, C46.2, C47.2, C48.2, C49.2, C50.2, C51.2, C52.2, C53.1, C54.1, C55.2, D1.2, D2.1 (K), D3.2 (A), D4.2, J1.5, JP12.1 (A), L5.2, L6.3 (GND), R3.2, R7.2, R10.2, R14.2, R16.2, R18.2, SW1.1, U1.1 (GND), U2.1 (VSS), U3.2 (GND), U4.1 (VSS), U5.2 (GND), U5.7 (EP), U6.2, U6.9, U6.10, U7.1, U7.2, U7.3, U7.4, U7.A1B12 (GND), U7.B1A12 (GND), U8.1 (CC2), U8.2 (GND), U8.3 (CC1), U8.10 (DB/), U8.12 (VCC), U8.13 (EP), U9.6 (GND), U9.10 (GND), U10.17 (VSSDSI), U10.23 (VSSDSI), U10.24 (VSS), U10.33 (VSSA), U10.40 (VSS), U10.54 (VSS), U10.66 (VSSSMPS), U10.68 (VSS), U10.82 (VSS), U10.88 (VSS), U10.94 (VSS), U10.110 (VSS), U10.130 (VSS), U10.143 (VSS), U11.15, U11.25, U11.26, U12.1 (GND), X2.2 (GND), X2.4 (GND)
GNDA: JP2.2 (B), L5.1, TP6.1
unnamed: D2.2 (A), R8.2
unnamed: C22.1, D5.1 (K), U8.8 (IN_GD)
unnamed: JP11.2 (B), U11.23
unnamed: JP12.2 (B), U11.24
unnamed: Q1.3 (D), R11.1
unnamed: C20.2, Q2.4 (G), U8.5 (GATE)
unnamed: R17.1, U11.13
unnamed: C3.1, L1.2, U1.3 (Vin)
unnamed: L2.1, U1.2 (Vout)
unnamed: C13.2, R6.2, R7.1, U3.5 (FB)
unnamed: L3.1, U3.3 (LX)
unnamed: C16.1, R9.1, U5.1 (EN)
unnamed: R13.2, R14.1, U8.6 (CTRLVBUS)
unnamed: TP19.1, U10.1 (PE2)
unnamed: TP20.1, U10.2 (PE3)
unnamed: TP21.1, U10.4 (PE5)
unnamed: TP22.1, U10.5 (PE6)
unnamed: R16.1, U10.138 (PH3)
unnamed: L7.1, U10.64 (VLXSMPS)
unnamed: R18.1, R19.1, U12.2 (RESET)

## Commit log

2025-08-11 [HW] [PCB] v0.1; initial commit
2025-08-11 [HW] [PCB] phase #2
2025-08-11 [HW] [PCB] v.01 phase #3
2025-08-11 [HW] [PCB] v0.1_Y48 revision
2025-08-11 [HW] [PCB] revision v0.1_Y49
2025-08-15 [HW] [PCB] PCB Revision 0.2_Y50; DK1
2025-08-18 [HW] [PCB] next iteratoonv, 1.0 board, dk2 candidate
2025-09-15 V1.0 rework to match stm32u5xxxQ
2025-09-25 Revision V2.0 finalized
2025-09-26 V2.0 Initial commit
2025-11-05 V2.0 Prototype Y61-9265739A
2025-11-23 backups, comments on schematic
2025-11-23 renaming projects
2025-11-23 Adding readme
